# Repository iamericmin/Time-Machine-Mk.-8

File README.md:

# Time Machine Mk. 8
Home of the Time Machine Mk. 8, a digital watch inspired by F1 and Neon Genesis Evangelion.

# Repo Map
TM8-firmware:
<<<<<<< HEAD
	- scratchpad: Arduino sketches for quick testing
	- TM8: PlatfomIO project directory.

TM8-hardware:
	- root: Contains current TM8 production files and top/bottom PNG renders
	- Prototypes: previous versions of TM8. Current versions in root directory.
	- Technical Drawings: PDFs of TM8 exported from Eagle
	- Cutting Board: old TM8 versions that were tossed away
	- dock: TM8 dock design files
	- Side projects: smaller side projects to go along with TM8.
=======
  1. scratchpad: Arduino sketches for quick testing
  2. TM8: PlatfomIO project directory.

TM8-hardware:
  1. root: Contains current TM8 production files and top/bottom PNG renders
  2. Prototypes: previous versions of TM8. Current versions in root directory.
  3. Technical Drawings: PDFs of TM8 exported from Eagle
  4. Cutting Board: old TM8 versions that were tossed away
  5. dock: TM8 dock design files
  6. Side projects: smaller side projects to go along with TM8.
>>>>>>> 88637fd49bccefb3e3033934de54475b4d8ace5f

Documentation directory will be created soon!

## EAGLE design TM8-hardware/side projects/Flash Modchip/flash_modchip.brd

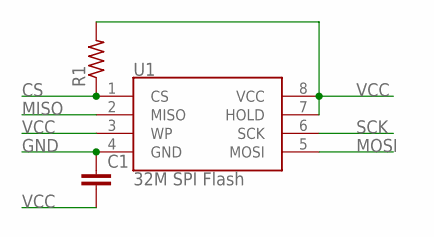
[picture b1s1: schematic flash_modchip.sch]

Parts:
C1: C-EUC0402; C0402
R1: R-US_R0402; R0402
U1: 32M SPI Flash; SO08

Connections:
CS: R1.1, U1.1 (CS)
GND: C1.1, U1.4 (GND)
MISO: U1.2 (MISO)
MOSI: U1.5 (MOSI)
SCK: U1.6 (SCK)
VCC: C1.2, R1.2, U1.3 (WP), U1.7 (HOLD), U1.8 (VCC)

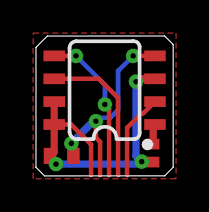
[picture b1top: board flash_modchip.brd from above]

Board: 2 copper layers, 7.6 x 7.8 mm, 3 parts (0 on the bottom side), 3 nets.

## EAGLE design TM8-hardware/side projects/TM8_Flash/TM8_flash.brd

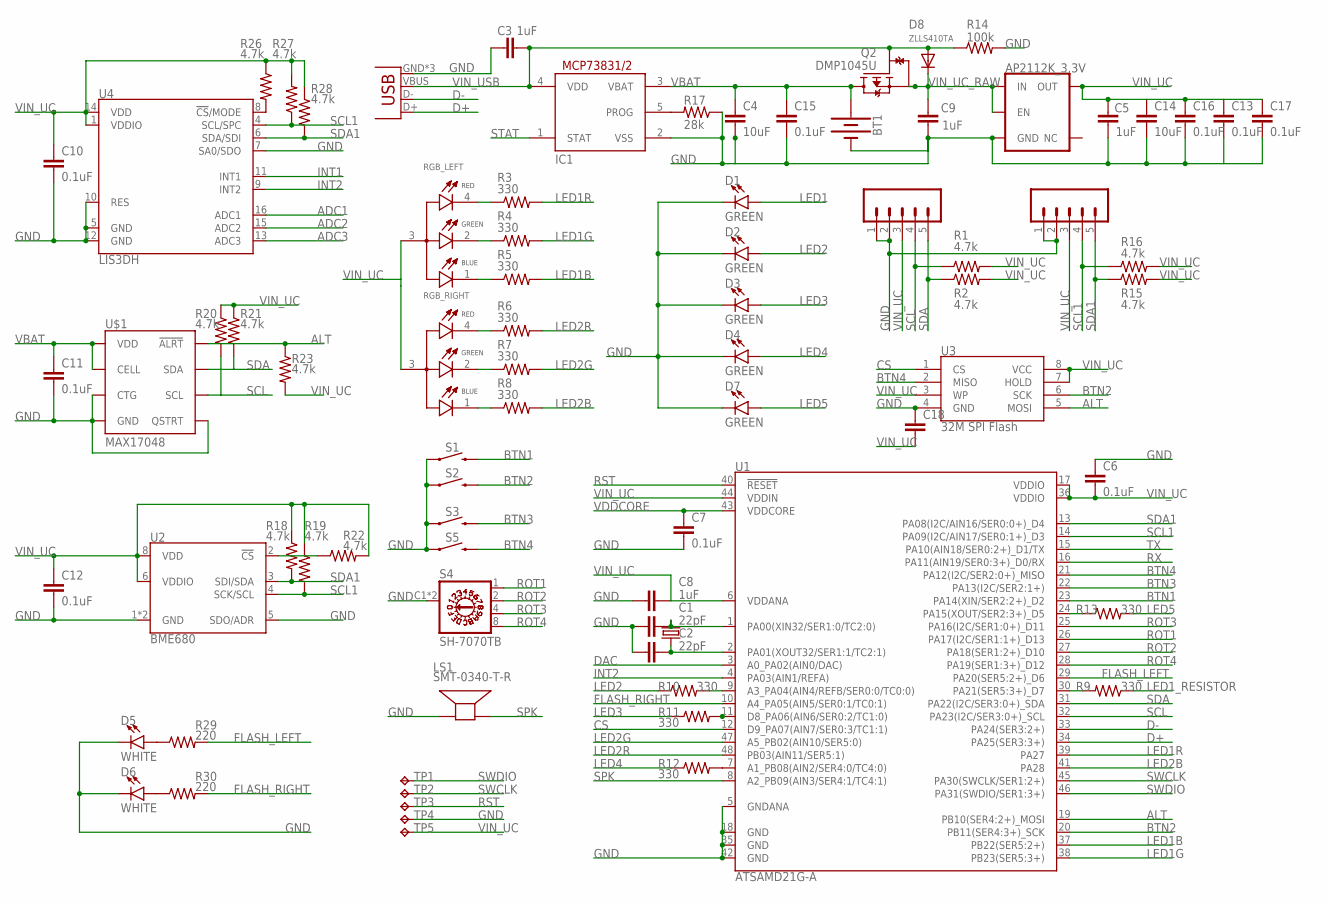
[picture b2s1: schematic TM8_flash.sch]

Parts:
AP2112K_3.3V: 3.3V; SOT23-5
BT1: BATTERY-20MM_SMD_4LEGS_OVERPASTE_INNER; BATTCON_20MM_4LEGS_OVERPASTE_INNER
C1, C2: 22pF; C0402
C3, C5, C8, C9: 1uF; C0402
C4, C14: 10uF; C0402
C6, C7, C10, C11, C12, C13, C15, C16, C17: 0.1uF; C0402
C18: C-EUC0402; C0402
D1, D2, D3, D4, D7: GREEN; LED-1206
D5, D6: WHITE; LED-1206
D8: ZLLS410TA; SOD-323F
IC1: MCP73831/OT; SOT23-5L
JP2: USB-MICROB
LCD1, LCD2: CONN_05VERT_FEMALE_HEADER; 1X05_SMD_VERTICAL_COMBO
LS1: SMT-0340-T-R; XDCR_SMT-0340-T-R
Q2: DMP1045U; SOT91P240X110-3N
R1, R2, R15, R16, R18, R19, R20, R21, R22, R23, R26, R27, R28: 4.7k; R0402
R3, R4, R5, R6, R7, R8, R9, R10, R11, R12, R13: 330; R0402
R14: 100k; R0402
R17: 28k; R0402
R29, R30: 220; R0402
RGB_LEFT: EAST1616RGBA3; LED_EAST1616RGBA3
RGB_RIGHT: EAST1616RGBA3; LED_EAST1616RGBA3
S1, S2, S3, S5: MOMENTARY-SWITCH-SPST-SMD-6.0X3.5MM; TACTILE_SWITCH_SMD_6.0X3.5MM
S4: SH-7070TB; SH-7070B
TP1, TP2, TP4, TP5: TPTP14R; TP14R
TP3: TPTP11R; TP11R
U1: ATSAMD21G-A; TQFP-48
U2: BME680; LGA3.0X3.0
U3: 32M SPI Flash; SO08
U4: LIS3DH; LGA-16-3X3
U$1: MAX17048; DFN-8
Y1: 32.768kHz; CRYSTAL-SMD-3.2X1.5MM

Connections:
ADC1: U4.16 (ADC1)
ADC2: U4.15 (ADC2)
ADC3: U4.13 (ADC3)
ALT: R23.1, U1.19 (PB10(SER4:2+)_MOSI), U3.5 (MOSI), U$1.P$5 (!ALRT)
BTN1: S1.2, U1.23 (PA14(XIN/SER2:2+)_D2)
BTN2: S2.2, U1.20 (PB11(SER4:3+)_SCK), U3.6 (SCK)
BTN3: S3.2, U1.22 (PA13(I2C/SER2:1+))
BTN4: S5.2, U1.21 (PA12(I2C/SER2:0+)_MISO), U3.2 (MISO)
CS: U1.12 (D9_PA07(AIN7/SER0:3/TC1:1)), U3.1 (CS)
D+: JP2.D+, U1.34 (PA25(SER3:3+))
D-: JP2.D-, U1.33 (PA24(SER3:2+))
DAC: U1.3 (A0_PA02(AIN0/DAC))
FLASH_LEFT: R29.2, U1.29 (PA20(SER5:2+)_D6)
FLASH_RIGHT: R30.2, U1.10 (A4_PA05(AIN5/SER0:1/TC0:1))
GND: AP2112K_3.3V.2 (GND), BT1.2 (-), C1.1, C2.1, C3.1, C4.2, C5.2, C6.1, C7.2, C8.1, C9.2, C10.2, C11.2, C12.2, C13.2, C14.2, C15.2, C16.2, C17.2, C18.1, D1.C, D2.C, D3.C, D4.C, D5.C, D6.C, D7.C, IC1.2 (VSS), JP2.GND, JP2.MT1 (GND), JP2.MT2 (GND), LCD1.1, LCD1.2, LCD2.1, LCD2.2, LS1.P, R14.2, R17.1, S1.1, S2.1, S3.1, S4.C1 (C), S4.C2 (C), S5.1, TP4.TP, U1.5 (GNDANA), U1.18 (GND), U1.35 (GND), U1.42 (GND), U2.1 (GND), U2.5 (SDO/ADR), U2.7 (GND), U3.4 (GND), U4.5 (GND), U4.7 (SA0/SDO), U4.10 (RES), U4.12 (GND), U$1.P$1 (CTG), U$1.P$4 (GND), U$1.P$6 (QSTRT), U$1.P$9 (GND)
INT1: U4.11 (INT1)
INT2: U1.4 (PA03(AIN1/REFA)), U4.9 (INT2)
LED1: D1.A
LED1B: R5.2, U1.37 (PB22(SER5:2+))
LED1G: R4.2, U1.38 (PB23(SER5:3+))
LED1R: R3.2, U1.39 (PA27)
LED1_RESISTOR: R9.1
LED2: D2.A, R10.1
LED2B: R8.2, U1.41 (PA28)
LED2G: R7.2, U1.47 (A5_PB02(AIN10/SER5:0))
LED2R: R6.2, U1.48 (PB03(AIN11/SER5:1))
LED3: D3.A, R11.1
LED4: D4.A, R12.1
LED5: D7.A, R13.2
unnamed: R12.2, U1.7 (A1_PB08(AIN2/SER4:0/TC4:0))
unnamed: R11.2, U1.11 (D8_PA06(AIN6/SER0:2/TC1:0))
unnamed: R9.2, U1.30 (PA21(SER5:3+)_D7)
unnamed: R10.2, U1.9 (A3_PA04(AIN4/REFB/SER0:0/TC0:0))
unnamed: R3.1, RGB_LEFT.4 (R_C)
unnamed: R4.1, RGB_LEFT.2 (G_C)
unnamed: R5.1, RGB_LEFT.1 (B_C)
unnamed: R6.1, RGB_RIGHT.4 (R_C)
unnamed: R7.1, RGB_RIGHT.2 (G_C)
unnamed: R8.1, RGB_RIGHT.1 (B_C)
unnamed: R13.1, U1.24 (PA15(XOUT/SER2:3+)_D5)
unnamed: IC1.5 (PROG), R17.2
unnamed: R22.1, U2.2 (!CS)
unnamed: D5.A, R29.1
unnamed: R26.2, U4.8 (!CS!/MODE)
unnamed: D6.A, R30.1
ROT1: S4.1, U1.26 (PA17(I2C/SER1:1+)_D13)
ROT2: S4.2, U1.27 (PA18(SER1:2+)_D10)
ROT3: S4.4, U1.25 (PA16(I2C/SER1:0+)_D11)
ROT4: S4.8, U1.28 (PA19(SER1:3+)_D12)
RST: TP3.TP, U1.40 (!RESET!)
RX: U1.16 (PA11(AIN19/SER0:3+)_D0/RX)
SCL: LCD1.4, R1.1, R20.2, U1.32 (PA23(I2C/SER3:0+)_SCL), U$1.P$7 (SCL)
SCL1: LCD2.4, R16.1, R19.2, R27.1, U1.14 (PA09(I2C/AIN17/SER0:1+)_D3), U2.4 (SCK/SCL), U4.4 (SCL/SPC)
SDA: LCD1.5, R2.1, R21.2, U1.31 (PA22(I2C/SER3:0+)_SDA), U$1.P$8 (SDA)
SDA1: LCD2.5, R15.1, R18.2, R28.2, U1.13 (PA08(I2C/AIN16/SER0:0+)_D4), U2.3 (SDI/SDA), U4.6 (SDA/SDI)
SPK: LS1.N, U1.8 (A2_PB09(AIN3/SER4:1/TC4:1))
STAT: IC1.1 (STAT)
SWCLK: TP2.TP, U1.45 (PA30(SWCLK/SER1:2+))
SWDIO: TP1.TP, U1.46 (PA31(SWDIO/SER1:3+))
TX: U1.15 (PA10(AIN18/SER0:2+)_D1/TX)
VBAT: BT1.1 (+), C4.1, C11.1, C15.1, IC1.3 (VBAT), Q2.3 (D), U$1.P$2 (CELL), U$1.P$3 (VDD)
VDDCORE: C7.1, U1.43 (VDDCORE)
VIN_UC: AP2112K_3.3V.5 (OUT), C5.1, C6.2, C8.2, C10.1, C12.1, C13.1, C14.1, C16.1, C17.1, C18.2, LCD1.3, LCD2.3, R1.2, R2.2, R15.2, R16.2, R18.1, R19.1, R20.1, R21.1, R22.2, R23.2, R26.1, R27.2, R28.1, RGB_LEFT.3 (A), RGB_RIGHT.3 (A), TP5.TP, U1.6 (VDDANA), U1.17 (VDDIO), U1.36 (VDDIO), U1.44 (VDDIN), U2.6 (VDDIO), U2.8 (VDD), U3.3 (WP), U3.7 (HOLD), U3.8 (VCC), U4.1 (VDDIO), U4.14 (VDD)
VIN_UC_RAW: AP2112K_3.3V.1 (IN), AP2112K_3.3V.3 (EN), C9.1, D8.C, Q2.2 (S)
VIN_USB: C3.2, D8.A, IC1.4 (VDD), JP2.VBUS, Q2.1 (G), R14.1
XIN32: C1.2, U1.1 (PA00(XIN32/SER1:0/TC2:0)), Y1.P$2 (2)
XOUT32: C2.2, U1.2 (PA01(XOUT32/SER1:1/TC2:1)), Y1.P$1 (1)

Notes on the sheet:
R14
R11
R12
R10
R13
R29
R30
R18
R19
R22
R23
R20
R21
R26
R27
R28

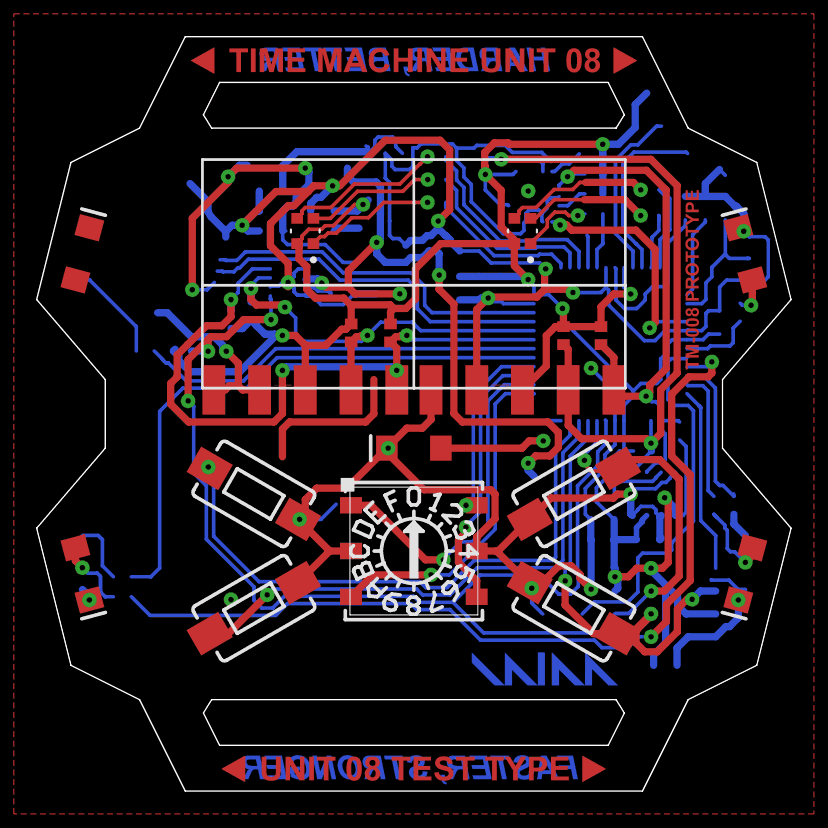
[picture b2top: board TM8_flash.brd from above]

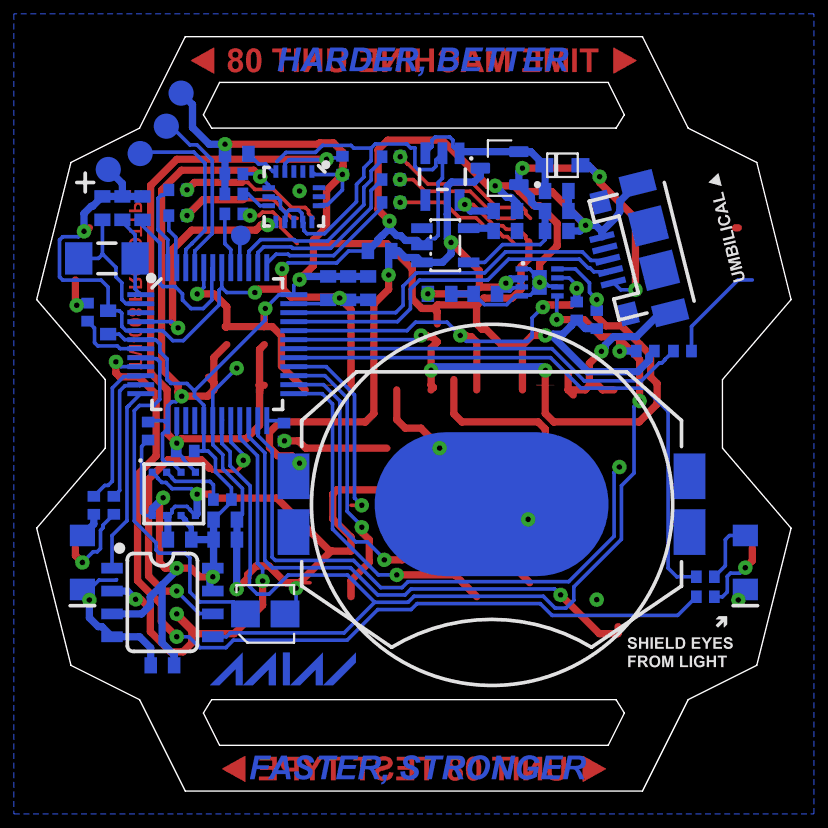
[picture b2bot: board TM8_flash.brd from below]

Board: 2 copper layers, 41.9 x 41.9 mm, 80 parts (62 on the bottom side), 57 nets.

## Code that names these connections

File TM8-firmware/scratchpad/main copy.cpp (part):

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const uint8_t rightG = A5;
const uint8_t rightB = 27;

const uint8_t btn1 = 2; // top left button
const uint8_t btn2 = 38;
const uint8_t btn3 = 24;
const uint8_t btn4 = 21;

const uint8_t led1 = 7; // top left LED
const uint8_t led2 = A3; // top left LED
const uint8_t led3 = A1; // top left LED
const uint8_t led4 = 8; // top left LED
const uint8_t led5 = 5; // center LED

const uint8_t rot1 = 13; // rotary bit 1
const uint8_t rot2 = 10; // rotary bit 2
const uint8_t rot4 = 11; // rotary bit 3
const uint8_t rot8 = 12; // rotary bit 4

// set time for RTC
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
  //bootUpSitRep();

  pinMode(btn1, INPUT_PULLUP);
  pinMode(btn2, INPUT_PULLUP);
  pinMode(btn3, INPUT_PULLUP);
  pinMode(btn4, INPUT_PULLUP);

  pinMode(leftR, OUTPUT);
  pinMode(leftG, OUTPUT);
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  // attachInterrupt(btn1, fuelInt, LOW);
  // attachInterrupt(btn2, setTimeInt, LOW);
  attachInterrupt(btn3, menuInt, LOW);
  //attachInterrupt(btn4, fuelInt, LOW); // for some reason enabling interrupts on this pin freezes the whole watch

  ADC->CTRLA.bit.ENABLE = 0;
  DAC->CTRLA.bit.ENABLE = 0;
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
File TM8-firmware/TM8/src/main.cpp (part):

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ExternalEEPROM rom;
TM8_util TM8;

// I found after lots of trial and error this is the only way to get TM8 to read PA12
// without the whole thing freezing or acting up
// returns 0 when closed, 1 when open
#define readBtn1 (PORT->Group[0].IN.reg & (1 << 14))
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#define readBtn3 (PORT->Group[1].IN.reg & (1 << 11))
#define readBtn4 (PORT->Group[0].IN.reg & (1 << 12))

const uint8_t btn1 = 2; // top left button
const uint8_t btn2 = 38; // bottom left button
const uint8_t btn3 = 24; // top right button
const uint8_t btn4 = 22; // bottom right button

const uint8_t leftBL = 26; // left backlight (red)
const uint8_t rightBL = 3; // right backlight (red)
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  Wire.begin();
  wire1.begin();

  // pinPeripheral(4, PIO_SERCOM); // SDA: D4 / PA08
  // pinPeripheral(3, PIO_SERCOM); // SCL: D3 / PA09

  TM8.dispStr("0nrg", 0);

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  delay(50);

  // enable pullups on all inputs to prevent floating
  pinMode(btn1, INPUT_PULLUP); // button 1, top left
  pinMode(btn2, INPUT_PULLUP); // button 2, bottom left
  pinMode(btn3, INPUT_PULLUP); // button 3, top right

  pinMode(6, OUTPUT); // flashlight
  pinMode(9, OUTPUT); // piezo
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    pinMode(leds[i], OUTPUT);
  }

  // enable pullups for PA12, sets it to input, writes HIGH to it
  // this is the only way to configure PA12 without having it freeze TM8
  PORT->Group[0].PINCFG[12].reg = PORT_PINCFG_PULLEN | PORT_PINCFG_INEN;
  PORT->Group[0].OUTSET.reg = PORT_PA12;

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
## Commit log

2023-05-18 fixed 'i' to be the same as '1'
2023-05-18 main program counter now starts from 1
2023-05-18 BTN4 now working with port manipulation
2023-05-19 added chronograph and started data recorder
2023-05-19 polished chrono and data recorder
2023-05-22 now you can adjust time!
2023-05-22 added comments for bootup animation function
2023-05-23 added MAX17048 library
2023-05-23 added race chrono, sort of
2023-06-17 got TM8's accelerometer to work!
2023-06-18 idfk
2023-06-26 added beeps
2023-06-26 optimized some stuff
2023-06-27 BME680 working. Ferrari F1 firing order
2023-07-29 added sobriety game
2023-08-30 updated with more stuff
2023-12-17 made firing anim idle limit to save power
2023-12-17 started work on cleaning up code. Will move helper functions to own lib
2023-12-17 split code more into two, LEDs don't work for some reason
2023-12-21 FINALLY got interupts working on btn2 and btn4
2023-12-21 added mouse jiggler
2023-12-22 Integrated mouse jiggler and lock screen shortcut into one app
2023-12-22 started pomodoro app
2024-01-03 pomodoro mostly working now
2024-06-13 asdf
2024-06-23 FW 1.8.3, added live temp reading and no seconds for longer battery life

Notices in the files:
parts and their libraries:
SparkFun-IC-Memory: Licensing: Creative Commons ShareAlike 4.0 International - https://creativecommons.org/licenses/by-sa/4.0
